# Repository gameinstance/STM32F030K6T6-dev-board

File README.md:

# STM32F030K6T6-dev-board
A barebone development board for STM32F030K6T6.

Details on: https://www.gameinstance.com/post/87/STM32F030K6T6-dev-board

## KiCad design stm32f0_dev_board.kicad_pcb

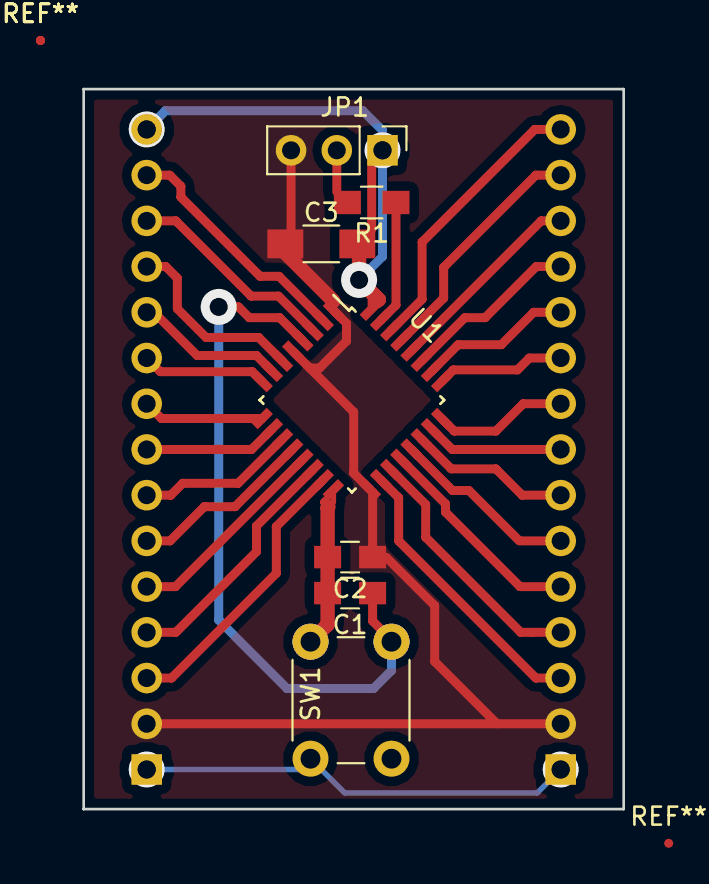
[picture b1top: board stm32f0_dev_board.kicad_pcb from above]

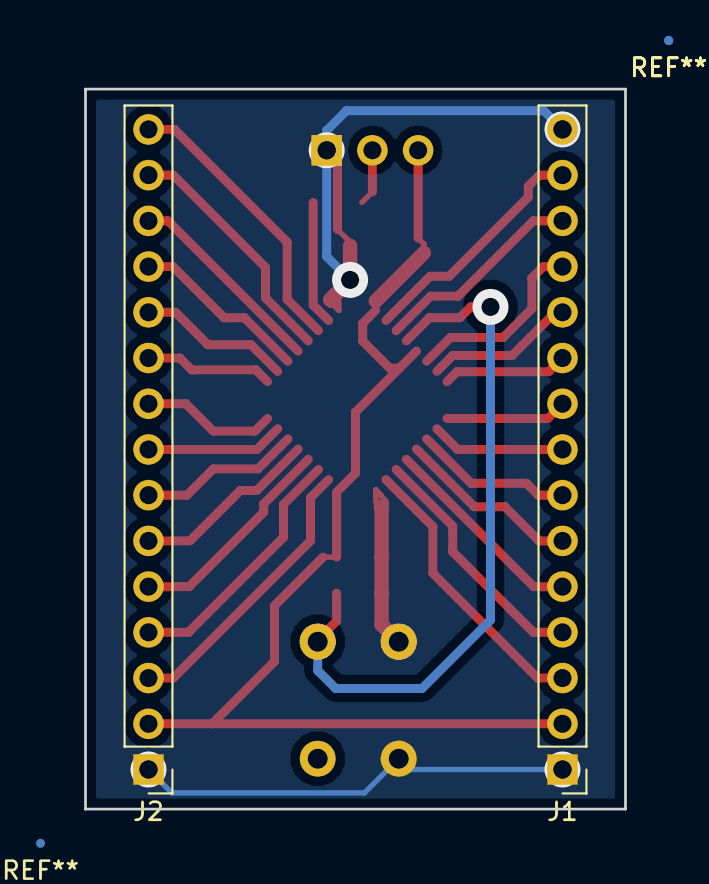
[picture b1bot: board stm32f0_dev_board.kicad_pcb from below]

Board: 2 copper layers, 30.0 x 40.0 mm, 9 parts (2 on the bottom side), 30 nets.

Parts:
C1, C2: 100nF; C_0805_HandSoldering
C3: 1uF; C_1206_HandSoldering
J1, J2: Conn_01x15_Male; Pin_Header_Straight_1x15_Pitch2.54mm
JP1: BOOT Seq; Pin_Header_Straight_1x03_Pitch2.54mm
R1: 10k; R_0805_HandSoldering
SW1: SW_SPST; SW_PUSH_6mm_h4.3mm
U1: STM32F030K6Tx; LQFP-32_7x7mm_Pitch0.8mm

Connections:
3V3: C2.1, C3.1, J1.2, J2.2, JP1.3, U1.1, U1.5, U1.17
GND: C1.2, C2.2, C3.2, J1.1, J1.15, J2.1, JP1.1, SW1.1, U1.16, U1.32
unnamed: C1.1, SW1.2, U1.4
unnamed: J1.3, U1.15
unnamed: J1.4, U1.14
unnamed: J1.5, U1.13
unnamed: J1.6, U1.12
unnamed: J1.7, U1.11
unnamed: J1.8, U1.10
unnamed: J1.9, U1.9
unnamed: J1.10, U1.8
unnamed: J1.11, U1.7
unnamed: J1.12, U1.6
unnamed: J1.13, U1.3
unnamed: J1.14, U1.2
unnamed: J2.3, U1.18
unnamed: J2.4, U1.19
unnamed: J2.5, U1.20
unnamed: J2.6, U1.21
unnamed: J2.7, U1.22
unnamed: J2.8, U1.23
unnamed: J2.9, U1.24
unnamed: J2.10, U1.25
unnamed: J2.11, U1.26
unnamed: J2.12, U1.27
unnamed: J2.13, U1.28
unnamed: J2.14, U1.29
unnamed: J2.15, U1.30
unnamed: JP1.2, R1.2
unnamed: R1.1, U1.31
